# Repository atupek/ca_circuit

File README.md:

# ca_circuit
These are the Logisim, KiCAD, and Arduino files for my elementary cellular automaton circuit.  For more information, see my blogpost at: http://annietupek.com/blog1/2016/04/27/elementary-cellular-automaton-circuit/

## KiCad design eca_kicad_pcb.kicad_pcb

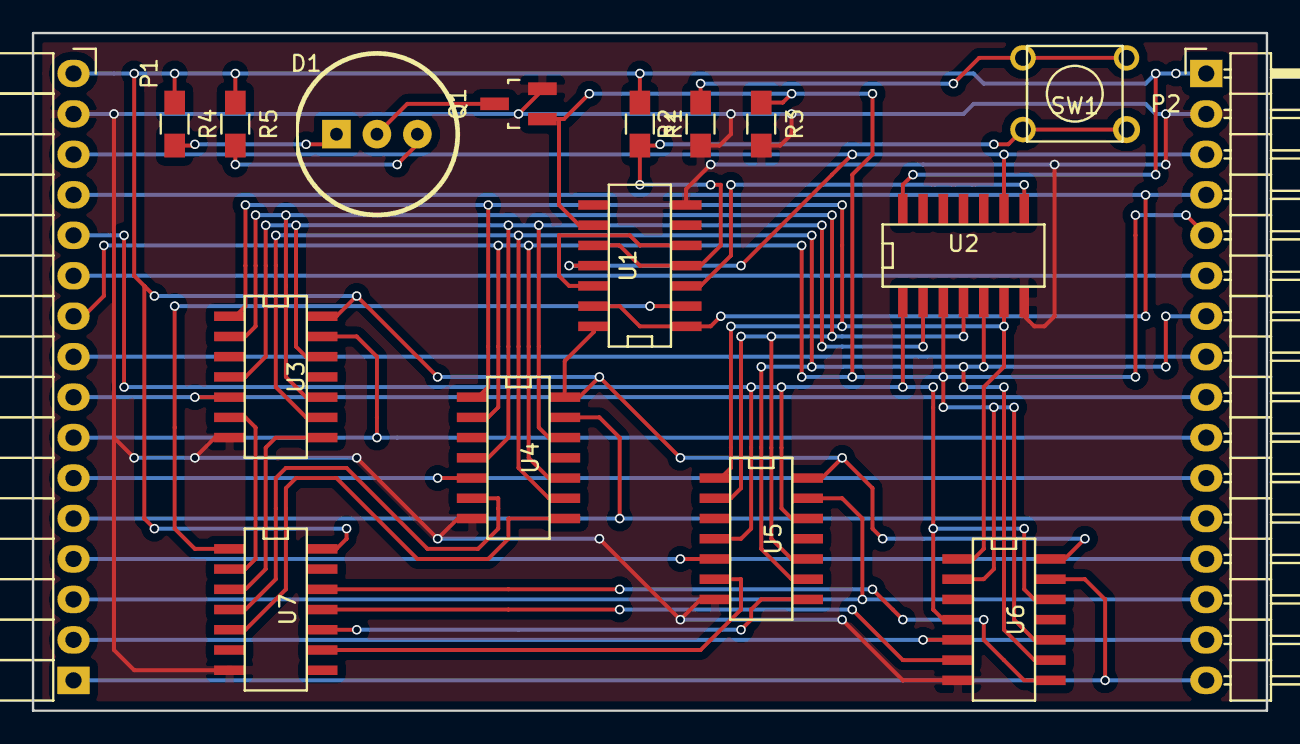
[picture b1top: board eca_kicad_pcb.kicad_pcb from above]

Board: 2 copper layers, 77.5 x 42.5 mm, 17 parts (0 on the bottom side), 36 nets.

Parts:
D1: Led_x2; LED-10MM-2
P1: lhs connectors; Socket_Strip_Angled_1x16_Rev_Pins
P2: rhs connectors; Pin_Header_Angled_1x16
Q1: Q_NMOS_GSD; SOT-23_Handsoldering
R1, R2, R3, R4, R5: R; R_0805_HandSoldering
SW1: SPST; 6x6_tactile_switch
U1: 74HC74; SOIC-14_Hand_Soldering
U2: 4069; SOIC-14_Hand_Soldering
U3, U4, U5, U6: 74LS21; SOIC-14_Hand_Soldering
U7: 4078; SOIC-14_Hand_Soldering

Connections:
+5V: P1.16, P2.1, R1.1, R4.1, R5.1, U1.14, U2.14, U3.14, U4.14, U5.14, U6.14, U7.14
/and0: U3.6, U7.2
/and1: U3.8, U7.3
/and2: U4.6, U7.4
/and3: U4.8, U7.5
/and4: U5.6, U7.9
/and5: U5.8, U7.10
/and6: U6.6, U7.11
/and7: U6.8, U7.12
/clock: P1.14, P2.3, U1.11, U2.9
/in_from_left: P1.12, U2.1, U5.4, U5.12, U6.4, U6.12
/in_from_right: P2.7, U2.5, U3.9, U4.9, U5.9, U6.9
/loop_left_to_right: P1.9, P2.8
/loop_right_to_left: P1.11, P2.6
/not_clock: U1.3, U2.8
/not_left: U2.2, U3.4, U3.12, U4.4, U4.12
/not_right: U2.6, U3.1, U4.1, U5.1, U6.1
/not_self: U2.4, U3.2, U3.10, U5.2, U5.10
/output: P1.10, P2.5, Q1.1, R3.1, U1.9, U2.3, U4.2, U4.10, U6.2, U6.10
/program0: P1.8, P2.9, U3.5
/program1: P1.7, P2.10, U3.13
/program2: P1.6, P2.11, U4.5
/program3: P1.5, P2.12, U4.13
/program4: P1.4, P2.13, U5.5
/program5: P1.3, P2.14, U5.13
/program6: P1.2, P2.15, U6.5
/program7: P1.1, P2.16, U6.13
/reset: P1.13, P2.4, U1.1, U1.13
/set: R1.2, SW1.1, U1.4, U1.10
/temp_output: U1.2, U7.1
GND: P1.15, P2.2, Q1.2, R2.1, R3.2, U1.7, U2.7, U3.7, U4.7, U5.7, U6.7, U7.7
unnamed: D1.1, R4.2
unnamed: D1.2, Q1.3
unnamed: D1.3, R5.2
unnamed: R2.2, SW1.2
unnamed: U1.5, U1.12
